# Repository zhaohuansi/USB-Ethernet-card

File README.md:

# USB-Ethernet-card
USB Ethernet card based on rtl8152b chip

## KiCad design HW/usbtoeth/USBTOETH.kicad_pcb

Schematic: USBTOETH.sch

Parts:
C1, C6: 4.7U; C_2010_5025Metric
C2, C3, C4, C5, C7, C8, C9, C11: 0.1U; C_2010_5025Metric
C10, C12: 1U; C_2010_5025Metric
C13: 0.01U; C_2010_5025Metric
C14: 1000P-SA; C_2010_5025Metric
C15, C16: 27P; C_2010_5025Metric
C17, C18, C19, C20: 0.1u; C_2010_5025Metric
J1: Connector_RJ45_Shielded; RJ45_Amphenol_RJHSE538X_TSLT
J2: USB_A; USB_Micro-B_Amphenol_10103594-0001LF_Horizontal
R1: 0; R_2010_5025Metric
R2: 2.49K; R_2010_5025Metric
R3, R4, R5, R6: 75-S6; R_2010_5025Metric
R7, R8, R9: 10K; R_2010_5025Metric
U1: RTL8152B; QFN-24-1EP_4x4mm_P0.5mm_EP2.7x2.7mm
U2: TS8121A; SOP-16_4.4x10.4mm_P1.27mm
Y1: Crystal_GND23; Crystal_SMD_5032-4Pin_5.0x3.2mm

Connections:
/AVDD3: C3.1, C4.1, C5.1, C6.1, U1.1 (AVDD33), U1.10 (AVDD33), U1.13 (DVDD33)
GND: C1.2, C2.2, C3.2, C4.2, C5.2, C6.2, C7.1, C8.2, C9.2, C10.2, C11.2, C12.2, C13.2, C15.1, C16.1, C17.2, C18.2, C19.1, C20.1, J2.4, R2.2, R7.1, R8.2, R9.1, U1.6 (U2GND), Y1.2, Y1.4
GNDS: C14.2, C17.1, C18.1, C19.2, C20.2, J1.9, J1.10, J1.11, J1.12, J1.SH, J2.5
unnamed: C1.1, C2.1, R1.1, U1.11 (VDD5)
unnamed: C7.2, C8.1, C9.1, C10.1, U1.9 (U2VDD10), U1.16 (DVDD10), U1.23 (AVDD10)
unnamed: C11.1, C12.1, U1.12 (DVDD10_UPS)
unnamed: C13.1, U2.2 (RCT), U2.7 (TCT)
unnamed: C14.1, R3.2, R4.2, R5.2, R6.2
unnamed: C15.2, U1.22 (CKXTAL2), Y1.1
unnamed: C16.2, U1.21 (CKXTAL1), Y1.3
unnamed: J1.1, U2.9 (TX-)
unnamed: J1.2, U2.11 (TX+)
unnamed: J1.3, U2.14 (RX-)
unnamed: J1.4, J1.5, R5.1
unnamed: J1.6, U2.16 (RX+)
unnamed: J1.7, J1.8, R6.1
unnamed: J2.1, R1.2
unnamed: J2.2, U1.8 (U2DP)
unnamed: J2.3, U1.7 (U2DM)
unnamed: R2.1, U1.24 (RSET)
unnamed: R3.1, U2.10 (TCT)
unnamed: R4.1, U2.15 (RCT)
unnamed: R7.2, U1.19 (LANWAKEB)
unnamed: R8.1, U1.14 (GPIO)
unnamed: R9.2, U1.18 (SPISDI/XTALDET)
unnamed: U1.2 (MDIP0), U2.8 (TD-)
unnamed: U1.3 (MDIN0), U2.6 (TD+)
unnamed: U1.4 (MDIP1), U2.3 (RD-)
unnamed: U1.5 (MDIN1), U2.1 (RD+)

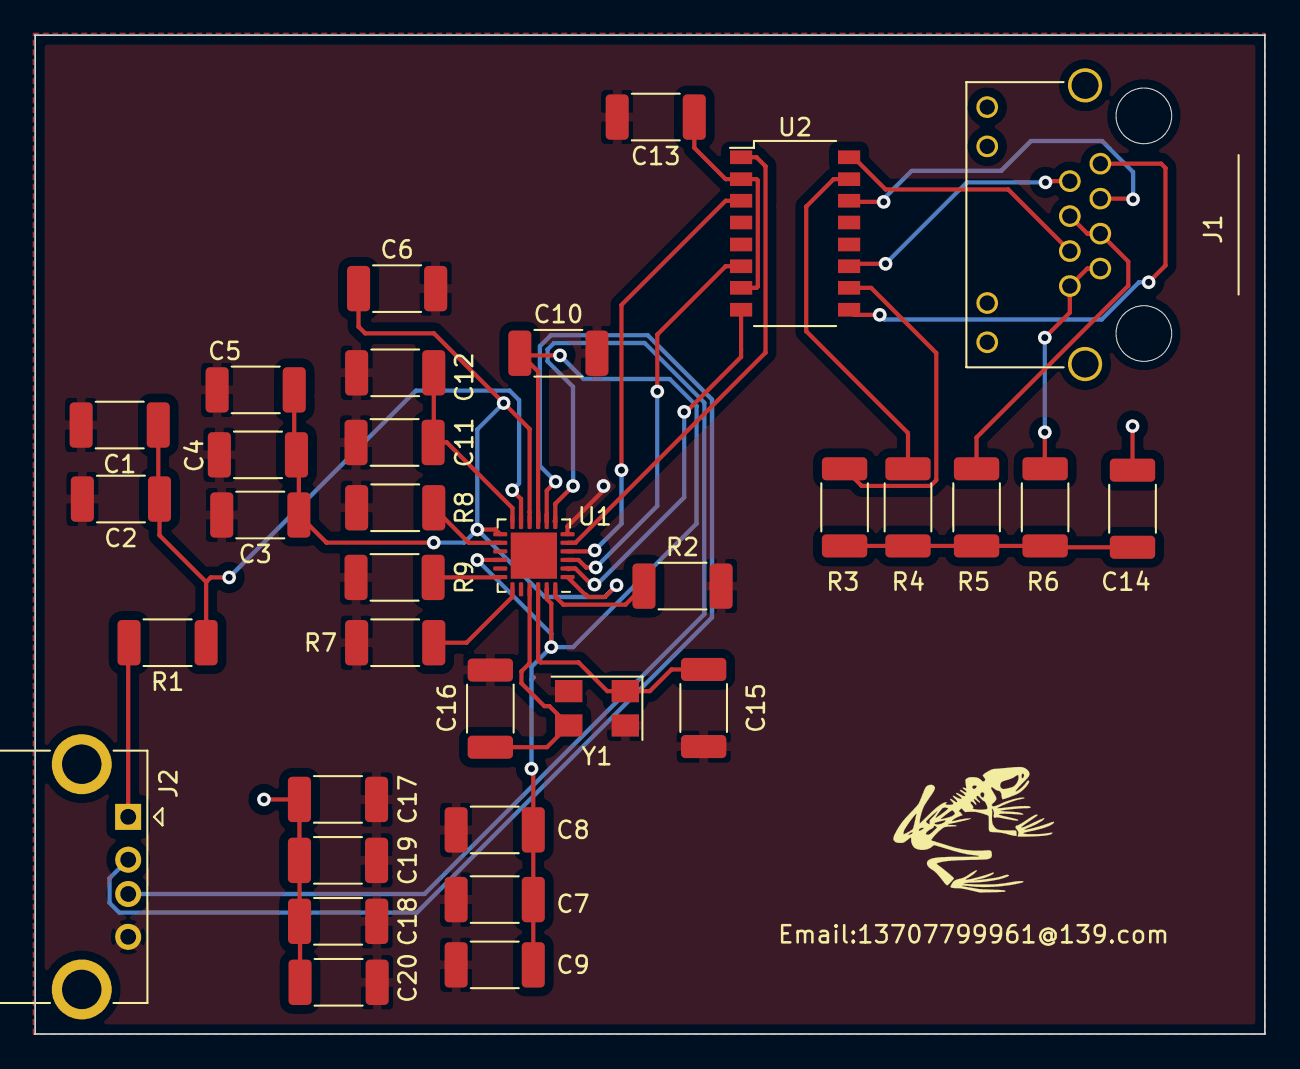
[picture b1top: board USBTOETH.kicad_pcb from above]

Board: 2 copper layers, 71.8 x 58.3 mm, 34 parts (0 on the bottom side), 29 nets.
